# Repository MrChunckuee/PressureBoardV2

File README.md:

# PressureBoardV2
Pressure Board

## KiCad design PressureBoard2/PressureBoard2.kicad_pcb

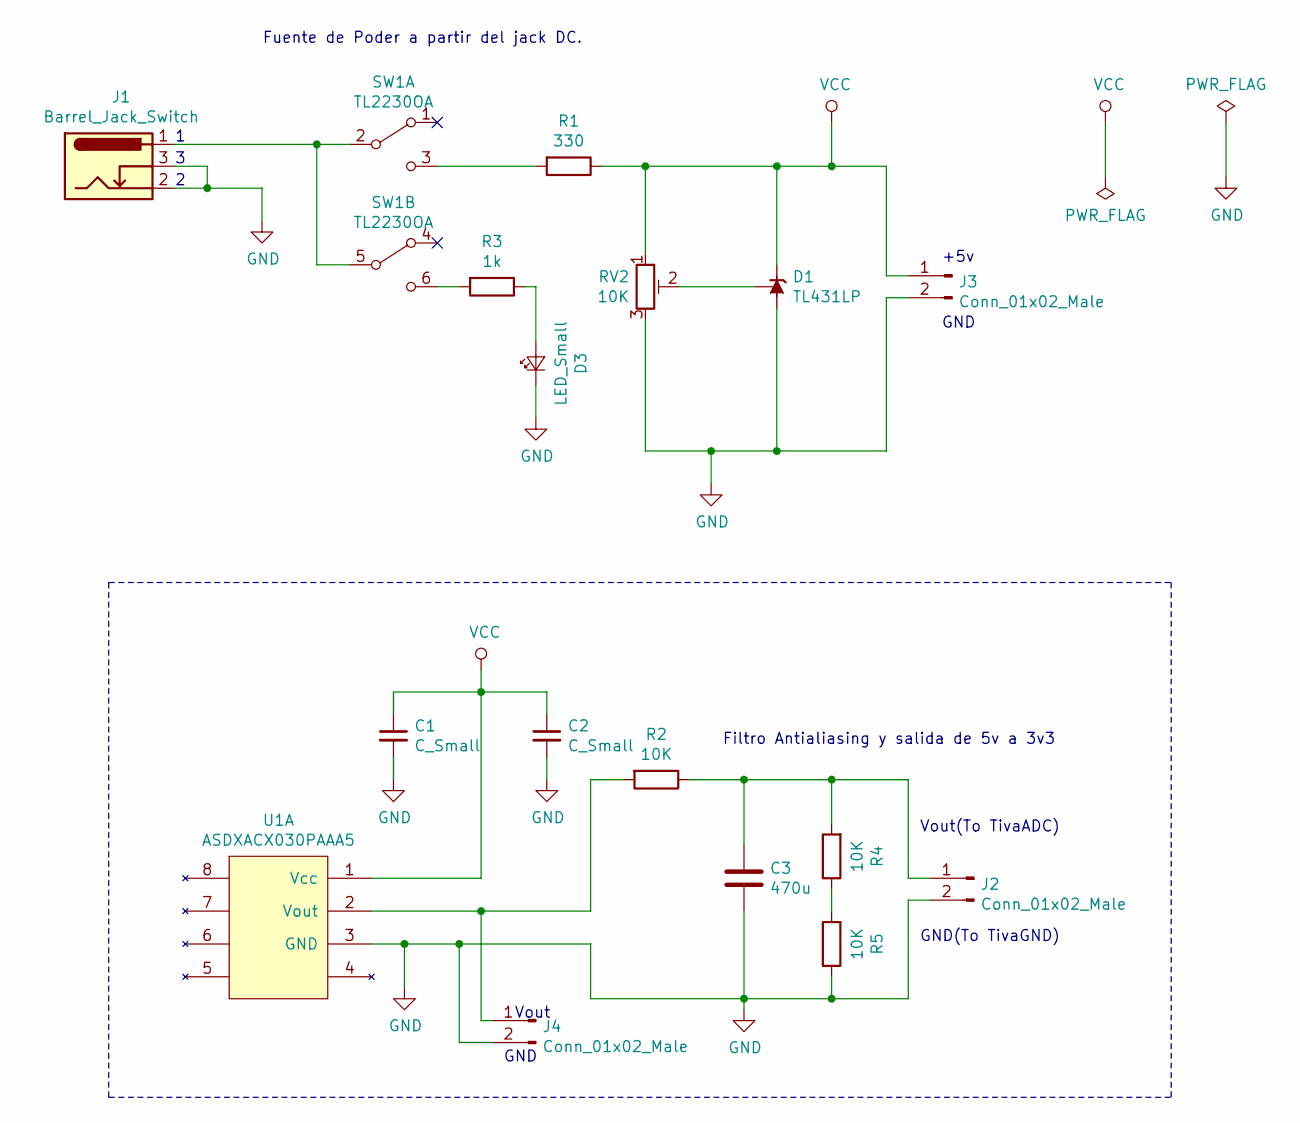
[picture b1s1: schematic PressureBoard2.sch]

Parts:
C1, C2: C_Small; C_Disc_D3.0mm_W1.6mm_P2.50mm
C3: 470u; C_Disc_D10.5mm_W5.0mm_P7.50mm; Mouser# 594-2222-368-25474; Digikey# BFC236825474-ND
D1: TL431LP; TO-92_Inline; Mouser# 595-TL431CLPR; Digikey# 296-1290-2-ND
D3: LED_Small; LED_D2.0mm_W4.8mm_H2.5mm_FlatTop
J1: Barrel_Jack_Switch; BarrelJack_Horizontal
J2, J3, J4: Conn_01x02_Male; PinHeader_1x02_P2.54mm_Vertical
R1: 330; Resistor_Horizontal_RM10mm
R2, R4, R5: 10K; Resistor_Horizontal_RM10mm
R3: 1k; Resistor_Horizontal_RM10mm
RV2: 10K; Potentiometer_Bourns_3296W_Vertical
SW1: TL2230OA; TL2230; Mouser# 629-GPBS-800L; Digikey# CW177-ND
U1: ASDXACX030PAAA5; Mouser# 785-ASDXACX030PAAA5; Digikey# 480-3749-ND

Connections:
GND: C1.2, C2.2, C3.2, D1.2 (A), D3.1 (K), J1.2, J1.3, J2.2, J3.2, J4.2, R5.1, RV2.3, U1.3 (GND)
unnamed: C3.1, J2.1, R2.1, R4.2
unnamed: D1.1 (REF), RV2.2
unnamed: D3.2 (A), R3.1
unnamed: J1.1, SW1.2 (B), SW1.5 (B)
unnamed: J4.1, R2.2, U1.2 (Vout)
unnamed: R1.2, SW1.3 (C)
unnamed: R3.2, SW1.6 (C)
unnamed: R4.1, R5.2
VCC: C1.1, C2.1, D1.3 (K), J3.1, R1.1, RV2.1, U1.1 (Vcc)

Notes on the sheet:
Fuente de Poder a partir del jack DC.
Filtro Antialiasing y salida de 5v a 3v3
Vout(To TivaADC)
GND(To TivaGND)
+5v
GND
Vout

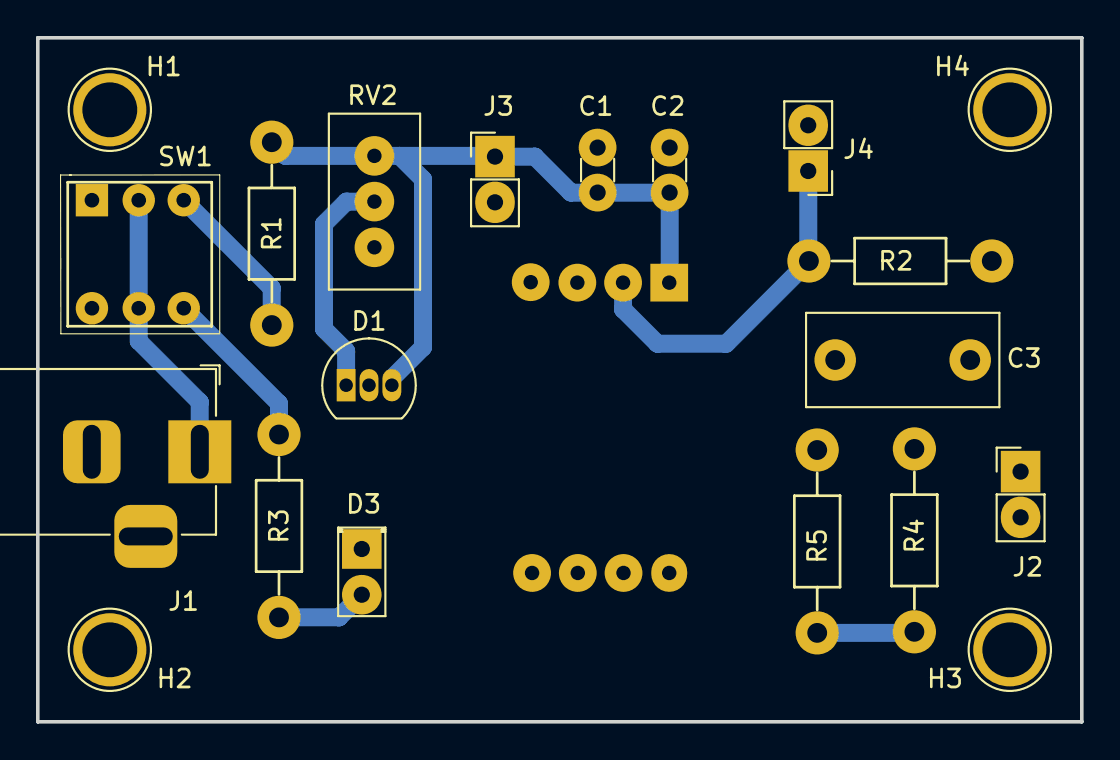
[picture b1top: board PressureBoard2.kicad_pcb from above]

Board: 2 copper layers, 58.0 x 38.0 mm, 21 parts (1 on the bottom side), 10 nets.

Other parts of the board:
H1, H2, H3, H4: 1pin

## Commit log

2019-04-05 Agrego primera versión del esquemático
2019-04-07 Agrego segunda versión del esquemático que, incluye: power jack, switch DPDT de 6 y led indicador de encendido.
2019-04-08 Agrego versión 3: Creación de footprint para ASDXACX030PAAA5, netlist de componentes y esquemático
2019-04-09 AGrego modificaciones en las dimesniones del sensor ASDX , en el netlist y la asignadión de footprints en el cvPCB.
2019-04-10 PCVBV1
    Agrego versión de PCB con ruteo y llenado de zonas de cobre.
2019-04-11 PCB_V3
    Agrego correcciones en footprints del ASDX, Switch DPDT y modificaciones en ruteo.
2019-04-12 Se mejoro el Layout
2019-04-12 PCB_v3.1 Se mejoro el Layout
